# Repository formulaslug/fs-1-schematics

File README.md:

# Summary
This repository contains Kicad schematics and PCB layouts for all electrical systems on FS-1.

# Getting Started
* Install the **Github Flavored Markdown** Chrome extension here: https://chrome.google.com/webstore/detail/github-flavored-markdown/faelggnmhofdamhdegcdhhemfokkfngk?hl=en
* Follow the [Getting Started with Electrical](https://drive.google.com/open?id=1L1viwzrDSNJtUvsPxIs5Tox_gefWKw_3um9R9QZQ264) document in the FS Wiki on the Team Drive.

# Schematics
* [AccumulatorBoardHV](AccumulatorBoardHV/README.md): Board containing Vicor and temperature system DCDC converters, 60V threshold circuit for accumulator indicators, and charging relays
* [AccumulatorBoardLV](AccumulatorBoardLV/README.md): Board containing BMS/temp/IMD fault latching and temperature system.
* [AccumulatorElectronics](AccumulatorElectronics/README.md): Wiring schematic of the Accumulator electronics area
* [BatteryTempMonitor](BatteryTempMonitor/README.md): Single-board temperature system implementation, now split between other Accumulator boards
* [Brake Light](Brake Light/README.md): Brake Light PCB
* [Dash](Dash/README.md): Wiring schematic for dash
* [DashSwitchbox](DashSwitchbox/README.md): Switchbox PCB for Dash
* [PEBoardHV](PEBoardHV/README.md): Board containing discharge circuitry and CAN isolation for Sevcons, as well as 60V threshold circuitry for TSAL
* [PEBoardLV](PEBoardLV/README.md): Board containing ECU, BSPD, and h-bridge to drive TSAL, RTDS, and brake light
* [PEBox](PEBox/README.md): Wiring schematic for power electronics
* [Temperature Shield](Temperature Shield/README.md): Battery Cell Shield, facilitates connections between batteries and the temperature/BMS system
* [TSAL](TSAL/README.md): Board containing TSAL oscillator and LEDs, as well as RTDS piezo

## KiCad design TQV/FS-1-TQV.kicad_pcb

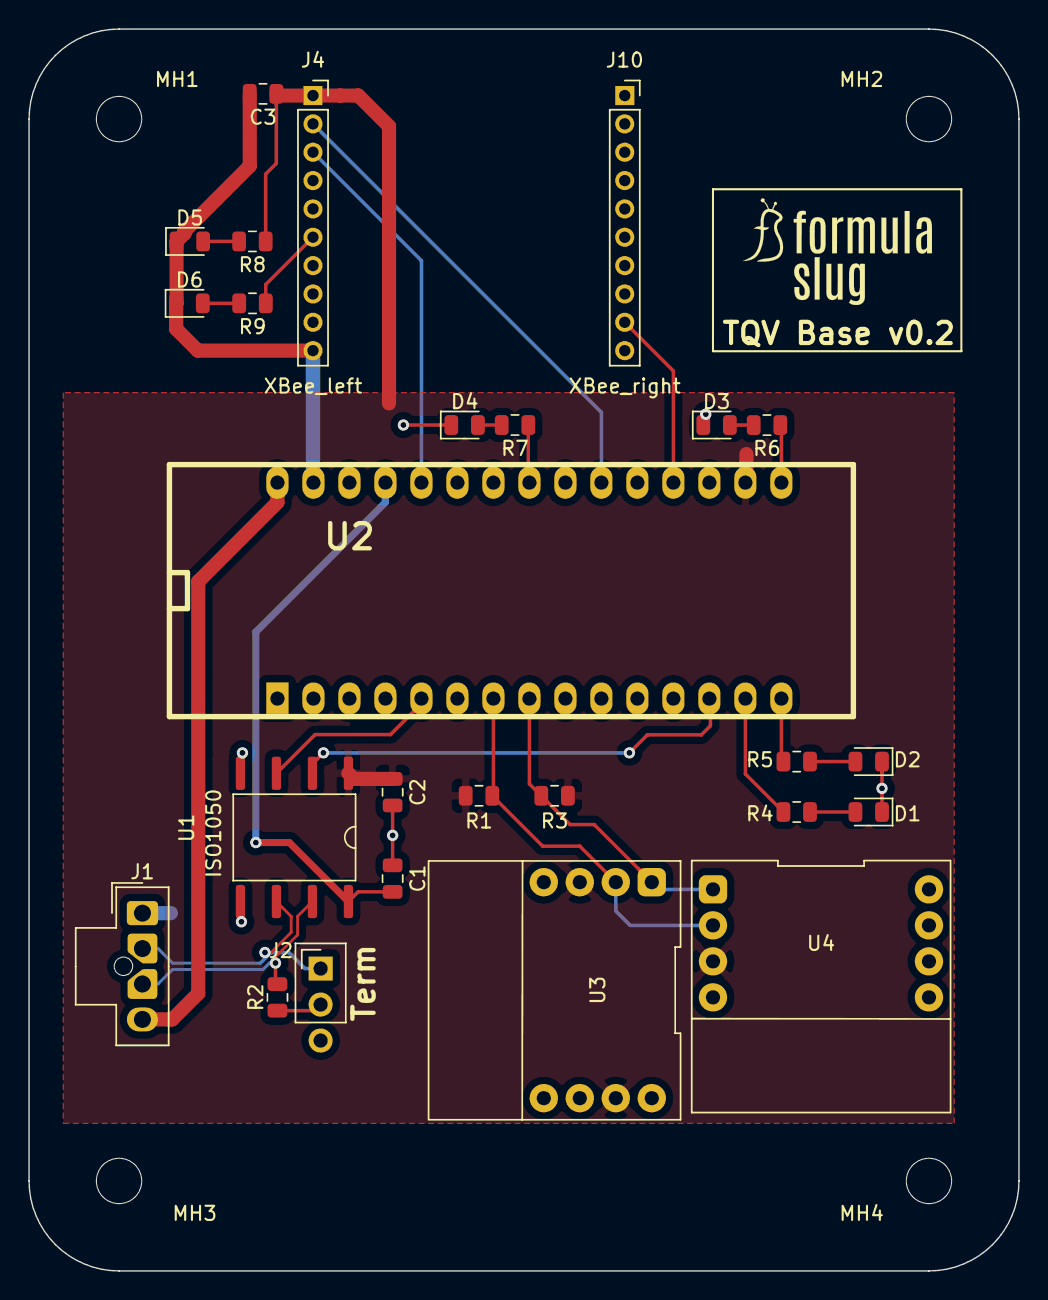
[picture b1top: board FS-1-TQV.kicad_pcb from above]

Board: 2 copper layers, 69.8 x 87.6 mm, 30 parts (0 on the bottom side), 25 nets.

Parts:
C1, C2: 1uF; C_0805_2012Metric
C3: 10uF; C_0805_2012Metric
D1, D2, D3, D4, D5, D6: LED; LED_0805_2012Metric
J1: CAN; Molex_Nano-Fit_1x04_P2.50mm_Vertical_Custom_Pads
J2: Conn_01x03_Male; PinHeader_1x03_P2.54mm_Vertical
J4: XBee_left; PinSocket_1x10_P2.00mm_Vertical
J10: XBee_right; PinSocket_1x10_P2.00mm_Vertical
MH1: MH1; MountingHole_3.2mm_M3
MH2: MH2; MountingHole_3.2mm_M3
MH3: MH3; MountingHole_3.2mm_M3
MH4: MH4; MountingHole_3.2mm_M3
R1, R3: 2k; R_0805_2012Metric
R2, R4, R5, R6, R7: 120; R_0805_2012Metric
R8, R9: 1k; R_0805_2012Metric
U1: ISO1050; SOP-8_6.62x9.15mm_P2.54mm
U2: stm_nucleo_F303K8_fstqv; arduino_mini
U3, U4: SparkFun_MPU9250; Sparkfun_MPU-9250

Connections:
+3V3: C2.2, C3.1, J4.1, R1.2, R3.2, R8.1, U1.1, U2.17, U3.3, U3.7, U4.3
/CAN_N: J1.2, J2.1, U1.6
/CAN_P: J1.3, R2.1, U1.7
GND: C1.2, C2.1, C3.2, D1.1, D2.1, D3.1, D4.1, D5.1, D6.1, J1.1, J4.10, U1.4, U1.5, U2.29, U3.4, U4.4, U4.7
unnamed: C1.1, U1.8, U2.27
unnamed: D1.2, R4.2
unnamed: D2.2, R5.2
unnamed: D3.2, R6.2
unnamed: D4.2, R7.2
unnamed: D5.2, R8.2
unnamed: D6.2, R9.2
unnamed: J1.4, U2.30
unnamed: J2.2, R2.2
unnamed: J4.2, U2.21
unnamed: J4.3, U2.26
unnamed: J4.6, R9.1
unnamed: J10.9, U2.19
unnamed: R1.1, U2.7, U3.2, U4.2
unnamed: R3.1, U2.8, U3.1, U4.1
unnamed: R4.1, U2.14
unnamed: R5.1, U2.15
unnamed: R6.1, U2.16
unnamed: R7.1, U2.23
unnamed: U1.2, U2.13
unnamed: U1.3, U2.5

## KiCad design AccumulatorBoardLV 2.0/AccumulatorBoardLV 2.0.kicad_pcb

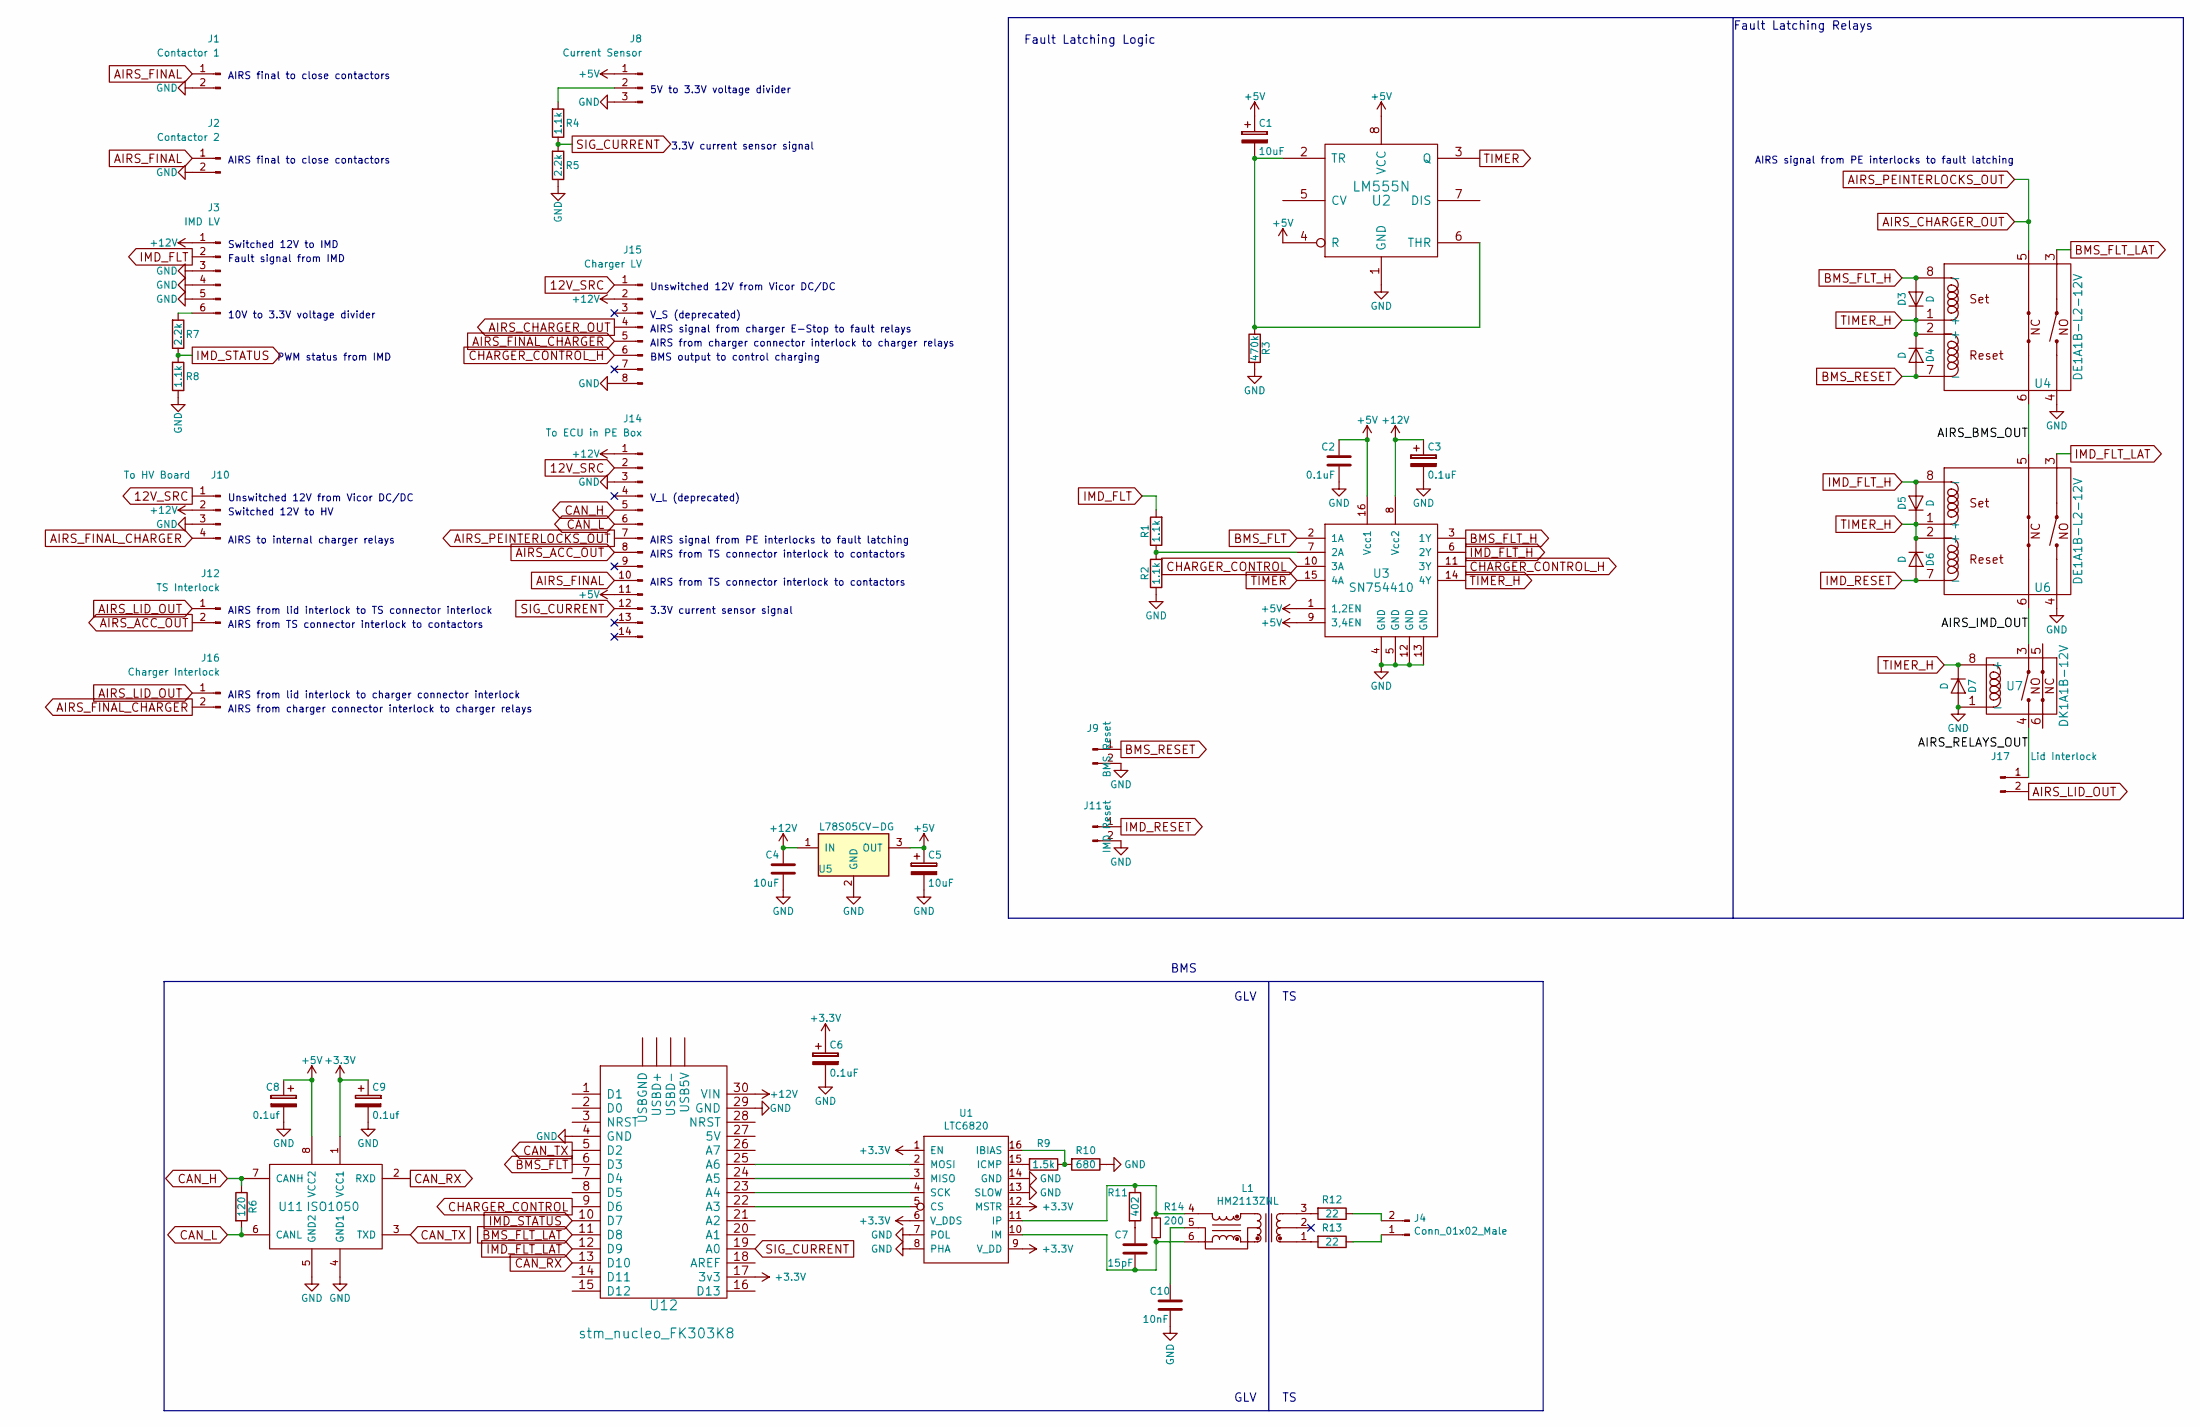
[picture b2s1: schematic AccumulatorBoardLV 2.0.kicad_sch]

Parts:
C1, C4, C5: 10uF; C_0805_HandSoldering
C2, C3, C6: 0.1uF; C_0805_HandSoldering
C7: 15pF; C_0805_HandSoldering
C8, C9: 0.1uf; C_0805_HandSoldering
C10: 10nF; C_0805_HandSoldering
D3, D4, D5, D6, D7: D; D_1206
J1: Contactor 1; Molex_NanoFit_1x02x2.50mm_Straight
J2: Contactor 2; Molex_NanoFit_1x02x2.50mm_Straight
J3: IMD LV; Molex_NanoFit_2x03x2.50mm_Straight
J4: Conn_01x02_Male; Molex_NanoFit_1x02x2.50mm_Straight
J8: Current Sensor; Molex_NanoFit_1x03x2.50mm_Straight
J9: BMS Reset; Molex_NanoFit_1x02x2.50mm_Straight
J10: To HV Board; Molex_NanoFit_2x02x2.50mm_Straight
J11: IMD Reset; Molex_NanoFit_1x02x2.50mm_Straight
J12: TS Interlock; Molex_NanoFit_1x02x2.50mm_Straight
J14: To ECU in PE Box; Ampseal-776261
J15: Charger LV; Ampseal-776276-1
J16: Charger Interlock; Molex_NanoFit_1x02x2.50mm_Straight
J17: Lid Interlock; Molex_NanoFit_1x02x2.50mm_Straight
L1: HM2113ZNL
R1, R2, R4, R8: 1.1k; R_0805_HandSoldering
R3: 470k; R_0805_HandSoldering
R5, R7: 2.2k; R_0805_HandSoldering
R6: 120; R_0805_HandSoldering
R9: 1.5k; R_0805_HandSoldering
R10: 680; R_0805_HandSoldering
R11: 402; R_0805_HandSoldering
R12, R13: 22; R_0805_HandSoldering
R14: 200; R_0805_2012Metric_Pad1.15x1.40mm_HandSolder
U1: LTC6820; MSOP-16_[LTC6820]_10_thou_compat
U2: LM555N; DIP-8_W7.62mm
U3: SN754410; DIP-16_W7.62mm
U4, U6: DE1A1B-L2-12V
U5: L78S05CV-DG; TO-220
U7: DK1A1B-12V
U11: ISO1050; DIP-8_W8.89mm_SMDSocket_LongPads
U12: stm_nucleo_FK303K8; arduino_mini

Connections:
12V_SRC: J10.1, J14.2, J15.1
+3V3: C6.1, C9.1, U1.1 (EN), U1.6 (V_DDS), U1.9 (V_DD), U1.12 (MSTR), U11.1 (VCC1), U12.17 (3v3)
+5V: C1.1, C2.1, C5.1, C8.1, J8.1, J14.11, U2.4 (R), U2.8 (VCC), U3.1 (1,2EN), U3.9 (3,4EN), U3.16 (Vcc1), U5.3 (OUT), U11.8 (VCC2)
+12V: C3.1, C4.1, J3.1, J10.2, J14.1, J15.2, U3.8 (Vcc2), U5.1 (IN), U12.30 (VIN)
/AIRS_BMS_OUT: U4.6, U6.5
/AIRS_IMD_OUT: U6.6, U7.3
/AIRS_RELAYS_OUT: J17.1, U7.4
AIRS_ACC_OUT: J12.2, J14.8
AIRS_CHARGER_OUT: J14.7, J15.4, U4.5
AIRS_FINAL: J1.1, J2.1, J14.10
AIRS_FINAL_CHARGER: J10.4, J15.5, J16.2
AIRS_LID_OUT: J12.1, J16.1, J17.2
BMS_FLT: U3.2 (1A), U12.6 (D3)
BMS_FLT_H: D3.2 (A), U3.3 (1Y), U4.8 (-)
BMS_FLT_LAT: U4.3, U12.11 (D8)
BMS_RESET: D4.2 (A), J9.1, U4.7 (-)
CAN_H: J14.5, R6.1, U11.7 (CANH)
CAN_L: J14.6, R6.2, U11.6 (CANL)
CAN_RX: U11.2 (RXD), U12.13 (D10)
CAN_TX: U11.3 (TXD), U12.5 (D2)
CHARGER_CONTROL: U3.10 (3A), U12.9 (D6)
CHARGER_CONTROL_H: J15.6, U3.11 (3Y)
GND: C2.2, C3.2, C4.2, C5.2, C6.2, C8.2, C9.2, C10.2, D7.2 (A), J1.2, J2.2, J3.3, J3.4, J3.5, J8.3, J9.2, J10.3, J11.2, J14.3, J15.8, R2.1, R3.2, R5.1, R8.1, R10.1, U1.7 (POL), U1.8 (PHA), U1.13 (SLOW), U1.14 (GND), U2.1 (GND), U3.4 (GND), U3.5 (GND), U3.12 (GND), U3.13 (GND), U4.4, U5.2 (GND), U6.4, U7.1 (-), U11.4 (GND1), U11.5 (GND2), U12.4 (GND), U12.29 (GND)
IMD_FLT: J3.2, R1.2
IMD_FLT_H: D5.2 (A), U3.6 (2Y), U6.8 (-)
IMD_FLT_LAT: U6.3, U12.12 (D9)
IMD_RESET: D6.2 (A), J11.1, U6.7 (-)
IMD_STATUS: R7.1, R8.2, U12.10 (D7)
unnamed: C1.2, R3.1, U2.2 (TR), U2.6 (THR)
unnamed: C7.1, R11.2
unnamed: C7.2, L1.6, R14.2, U1.10 (IM)
unnamed: C10.1, L1.5
unnamed: J3.6, R7.2
unnamed: J4.1, R13.1
unnamed: J4.2, R12.1
unnamed: J8.2, R4.2
unnamed: L1.1, R13.2
unnamed: L1.3, R12.2
unnamed: L1.4, R11.1, R14.1, U1.11 (IP)
unnamed: R1.1, R2.2, U3.7 (2A)
unnamed: R9.2, U1.15 (ICMP)
unnamed: R9.1, R10.2, U1.16 (IBIAS)
unnamed: U1.2 (MOSI), U12.25 (A6)
unnamed: U1.3 (MISO), U12.24 (A5)
unnamed: U1.4 (SCK), U12.23 (A4)
unnamed: U1.5 (CS), U12.22 (A3)
SIG_CURRENT: J14.12, R4.1, R5.2, U12.19 (A0)
TIMER: U2.3 (Q), U3.15 (4A)
TIMER_H: D3.1 (K), D4.1 (K), D5.1 (K), D6.1 (K), D7.1 (K), U3.14 (4Y), U4.1 (+), U4.2 (+), U6.1 (+), U6.2 (+), U7.8 (+)

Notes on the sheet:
AIRS signal from PE interlocks to fault latching
AIRS from charger connector interlock to charger relays
AIRS final to close contactors
AIRS from TS connector interlock to contactors
10V to 3.3V voltage divider
AIRS signal from charger E-Stop to fault relays
Unswitched 12V from Vicor DC/DC
3.3V current sensor signal
PWM status from IMD
V_L (deprecated)
V_S (deprecated)
GLV TS
AIRS to internal charger relays
BMS output to control charging
AIRS from lid interlock to TS connector interlock
Switched 12V to HV
BMS
5V to 3.3V voltage divider
AIRS from lid interlock to charger connector interlock
Fault Latching Relays
Fault Latching Logic
Switched 12V to IMD
Fault signal from IMD

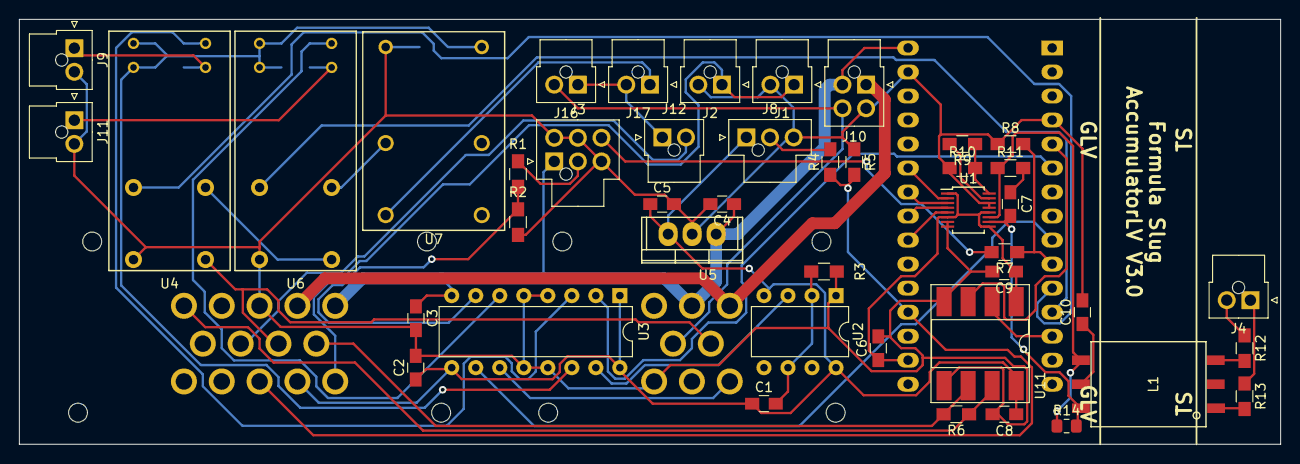
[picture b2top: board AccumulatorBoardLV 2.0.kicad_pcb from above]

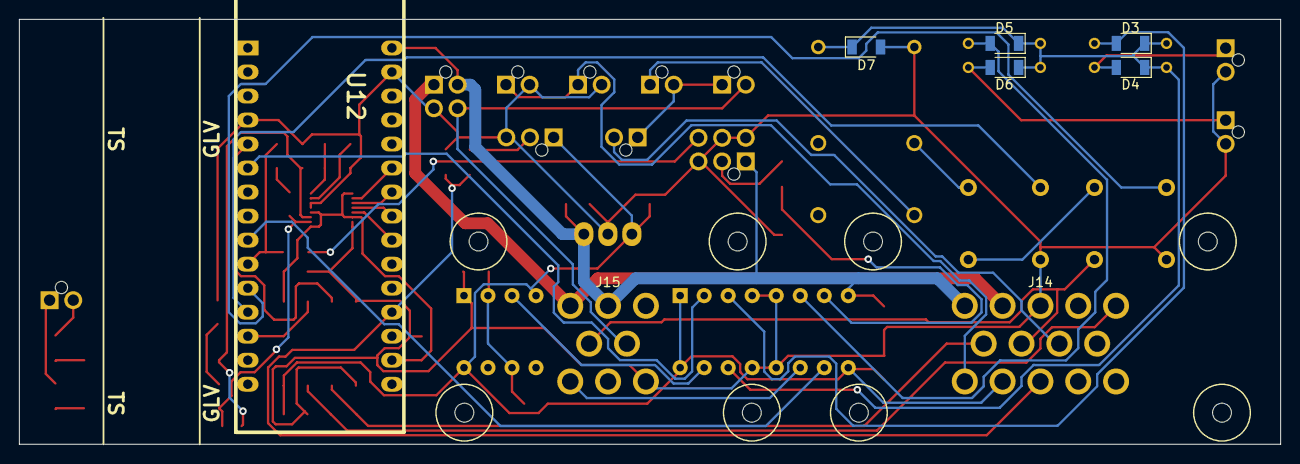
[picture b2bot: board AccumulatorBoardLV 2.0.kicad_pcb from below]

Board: 2 copper layers, 133.4 x 44.9 mm, 52 parts (8 on the bottom side), 49 nets.

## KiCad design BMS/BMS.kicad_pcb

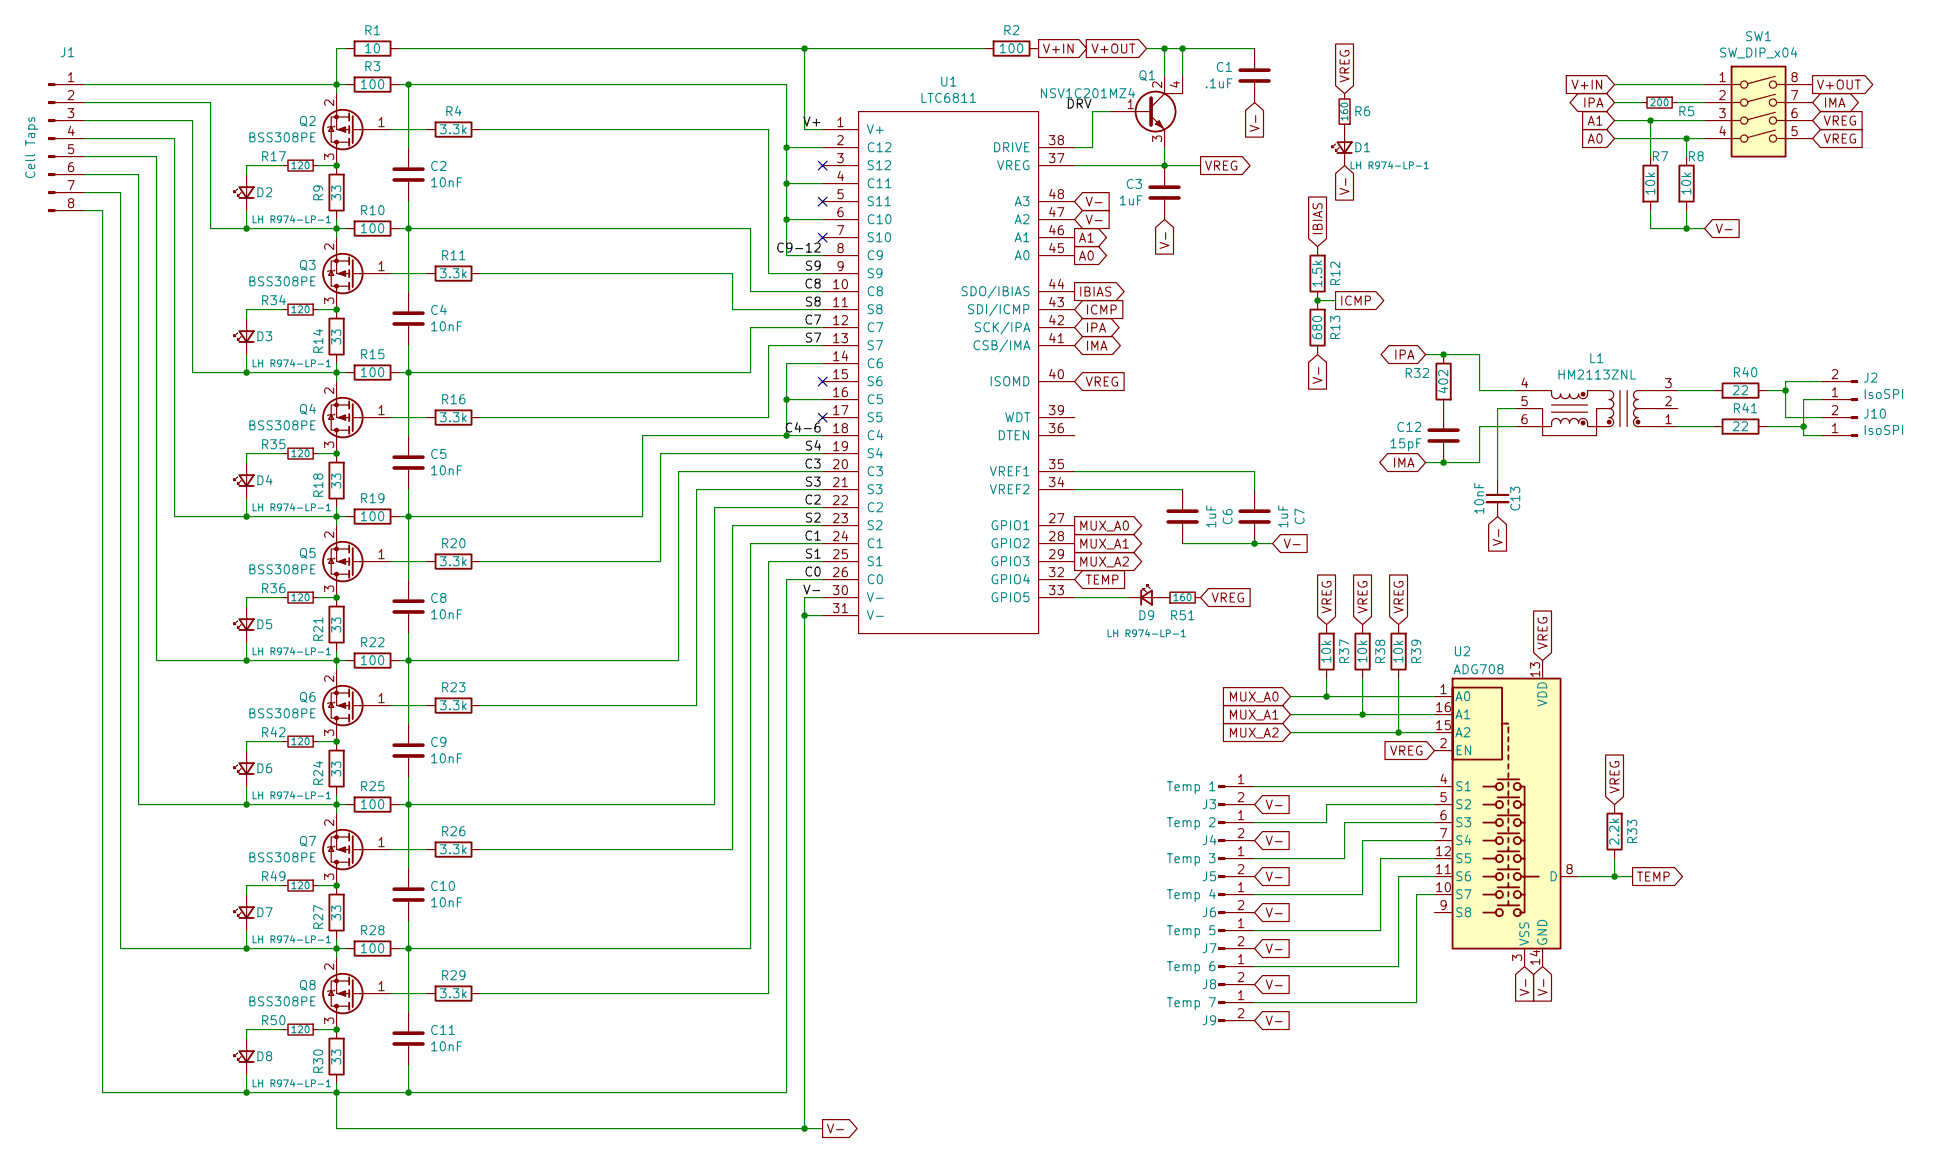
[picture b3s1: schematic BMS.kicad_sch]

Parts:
C1: .1uF; C_0805_HandSoldering
C2, C4, C5, C8, C9, C10, C11, C13: 10nF; C_0805_HandSoldering
C3, C6, C7: 1uF; C_0805_HandSoldering
C12: 15pF; C_0805_HandSoldering
D1, D2, D3, D4, D5, D6, D7, D8, D9: LH R974-LP-1; LED_0805_HandSoldering
J1: Cell Taps
J2, J10: IsoSPI; Molex_NanoFit_1x02x2.50mm_Straight
J3: Temp 1; Molex_NanoFit_1x02x2.50mm_Straight
J4: Temp 2; Molex_NanoFit_1x02x2.50mm_Straight
J5: Temp 3; Molex_NanoFit_1x02x2.50mm_Straight
J6: Temp 4; Molex_NanoFit_1x02x2.50mm_Straight
J7: Temp 5; Molex_NanoFit_1x02x2.50mm_Straight
J8: Temp 6; Molex_NanoFit_1x02x2.50mm_Straight
J9: Temp 7; Molex_NanoFit_1x02x2.50mm_Straight
L1: HM2113ZNL
Q1: NSV1C201MZ4; SOT-223
Q2, Q3, Q4, Q5, Q6, Q7, Q8: BSS308PE; SOT-23
R1: 10; R_0805_HandSoldering
R2, R3, R10, R15, R19, R22, R25, R28: 100; R_0805_HandSoldering
R4, R11, R16, R20, R23, R26, R29: 3.3k; R_0805_HandSoldering
R5: 200; R_0805_HandSoldering
R6, R51: 160; R_0805_HandSoldering
R7, R8, R37, R38, R39: 10k; R_0805_HandSoldering
R9, R14, R18, R21, R24, R27, R30: 33; R_2512_HandSoldering
R12: 1.5k; R_0805_HandSoldering
R13: 680; R_0805_HandSoldering
R17, R34, R35, R36, R42, R49, R50: 120; R_0805_HandSoldering
R32: 402; R_0805_HandSoldering
R33: 2.2k; R_0805_HandSoldering
R40, R41: 22; R_0805_HandSoldering
SW1: SW_DIP_x04; DIP A6H-4101
U1: LTC6811; FSOP-48_[LTC6811-2]
U2: ADG708; TSSOP-16_4.4x5mm_Pitch0.65mm

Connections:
/C1: C10.2, C11.1, R28.1, U1.24 (C1)
/C2: C9.2, C10.1, R25.1, U1.22 (C2)
/C3: C8.2, C9.1, R22.1, U1.20 (C3)
/C4-6: C5.2, C8.1, R19.1, U1.14 (C6), U1.16 (C5), U1.18 (C4)
/C7: C4.2, C5.1, R15.1, U1.12 (C7)
/C8: C2.2, C4.1, R10.1, U1.10 (C8)
/C9-12: C2.1, R3.1, U1.2 (C12), U1.4 (C11), U1.6 (C10), U1.8 (C9)
/DRV: Q1.1 (B), U1.38 (DRIVE)
/S1: R29.1, U1.25 (S1)
/S2: R26.1, U1.23 (S2)
/S3: R23.1, U1.21 (S3)
/S4: R20.1, U1.19 (S4)
/S7: R16.1, U1.13 (S7)
/S8: R11.1, U1.11 (S8)
/S9: R4.1, U1.9 (S9)
/V+: R1.1, R2.2, U1.1 (V+)
A0: R8.1, SW1.4, U1.45 (A0)
A1: R7.1, SW1.3, U1.46 (A1)
IBIAS: R12.2, U1.44 (SDO/IBIAS)
ICMP: R12.1, R13.2, U1.43 (SDI/ICMP)
IMA: C12.1, L1.6, SW1.7, U1.41 (CSB/IMA)
IPA: L1.4, R5.2, R32.1, U1.42 (SCK/IPA)
MUX_A0: R37.1, U1.27 (GPIO1), U2.1 (A0)
MUX_A1: R38.1, U1.28 (GPIO2), U2.16 (A1)
MUX_A2: R39.1, U1.29 (GPIO3), U2.15 (A2)
unnamed: C6.2, U1.34 (VREF2)
unnamed: C7.2, U1.35 (VREF1)
unnamed: C12.2, R32.2
unnamed: C13.1, L1.5
unnamed: D1.2 (A), R6.1
unnamed: D2.1 (K), J1.2, Q3.2 (S), R9.1, R10.2
unnamed: D2.2 (A), R17.2
unnamed: D3.1 (K), J1.3, Q4.2 (S), R14.1, R15.2
unnamed: D3.2 (A), R34.2
unnamed: D4.1 (K), J1.4, Q5.2 (S), R18.1, R19.2
unnamed: D4.2 (A), R35.2
unnamed: D5.1 (K), J1.5, Q6.2 (S), R21.1, R22.2
unnamed: D5.2 (A), R36.2
unnamed: D6.1 (K), J1.6, Q7.2 (S), R24.1, R25.2
unnamed: D6.2 (A), R42.2
unnamed: D7.1 (K), J1.7, Q8.2 (S), R27.1, R28.2
unnamed: D7.2 (A), R49.2
unnamed: D8.2 (A), R50.2
unnamed: D9.1 (K), U1.33 (GPIO5)
unnamed: D9.2 (A), R51.1
unnamed: J1.1, Q2.2 (S), R1.2, R3.2
unnamed: J3.1, U2.4 (S1)
unnamed: J4.1, U2.5 (S2)
unnamed: J5.1, U2.6 (S3)
unnamed: J6.1, U2.7 (S4)
unnamed: J7.1, U2.12 (S5)
unnamed: J8.1, U2.11 (S6)
unnamed: J9.1, U2.10 (S7)
unnamed: J2.1, J10.1, R41.1
unnamed: J2.2, J10.2, R40.1
unnamed: L1.1, R41.2
unnamed: L1.3, R40.2
unnamed: Q2.1 (G), R4.2
unnamed: Q2.3 (D), R9.2, R17.1
unnamed: Q3.1 (G), R11.2
unnamed: Q3.3 (D), R14.2, R34.1
unnamed: Q4.1 (G), R16.2
unnamed: Q4.3 (D), R18.2, R35.1
unnamed: Q5.1 (G), R20.2
unnamed: Q5.3 (D), R21.2, R36.1
unnamed: Q6.1 (G), R23.2
unnamed: Q6.3 (D), R24.2, R42.1
unnamed: Q7.1 (G), R26.2
unnamed: Q7.3 (D), R27.2, R49.1
unnamed: Q8.1 (G), R29.2
unnamed: Q8.3 (D), R30.2, R50.1
unnamed: R5.1, SW1.2
TEMP: R33.1, U1.32 (GPIO4), U2.8 (D)
V+IN: R2.1, SW1.1
V+OUT: C1.1, Q1.2 (C), Q1.4 (C), SW1.8
V-: C1.2, C3.2, C6.1, C7.1, C11.2, C13.2, D1.1 (K), D8.1 (K), J1.8, J3.2, J4.2, J5.2, J6.2, J7.2, J8.2, J9.2, R7.2, R8.2, R13.1, R30.1, U1.26 (C0), U1.30 (V-), U1.31 (V-), U1.47 (A2), U1.48 (A3), U2.3 (VSS), U2.14 (GND)
VREG: C3.1, Q1.3 (E), R6.2, R33.2, R37.2, R38.2, R39.2, R51.2, SW1.5, SW1.6, U1.37 (VREG), U1.40 (ISOMD), U2.2 (EN), U2.13 (VDD)

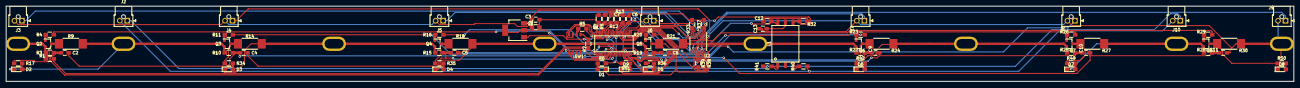
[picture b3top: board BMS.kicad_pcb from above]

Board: 2 copper layers, 428.0 x 25.0 mm, 88 parts (0 on the bottom side), 77 nets.

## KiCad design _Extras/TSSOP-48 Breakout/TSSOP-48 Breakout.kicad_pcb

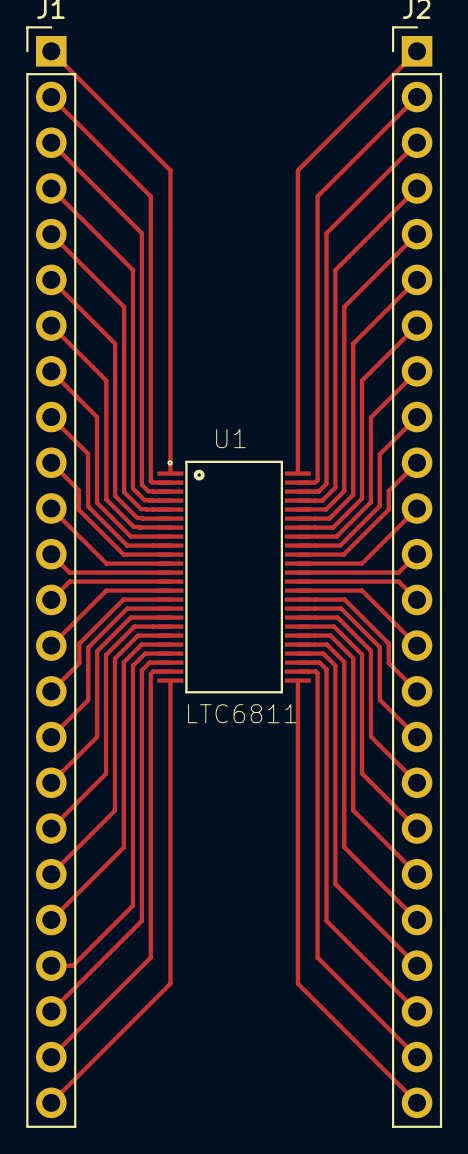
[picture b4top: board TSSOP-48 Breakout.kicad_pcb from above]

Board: 2 copper layers, 3 parts (0 on the bottom side), 48 nets.

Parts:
J1, J2: Conn_01x24_Male; Pin_Header_Straight_1x24_Pitch2.54mm
U1: LTC6811; FSOP-48_[LTC6811-2]_10_thou_compat

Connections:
1: J1.1, U1.1
2: J1.2, U1.2
3: J1.3, U1.3
4: J1.4, U1.4
5: J1.5, U1.5
6: J1.6, U1.6
7: J1.7, U1.7
8: J1.8, U1.8
9: J1.9, U1.9
10: J1.10, U1.10
11: J1.11, U1.11
12: J1.12, U1.12
13: J1.13, U1.13
14: J1.14, U1.14
15: J1.15, U1.15
16: J1.16, U1.16
17: J1.17, U1.17
18: J1.18, U1.18
19: J1.19, U1.19
20: J1.20, U1.20
21: J1.21, U1.21
22: J1.22, U1.22
23: J1.23, U1.23
24: J1.24, U1.24
25: J2.24, U1.25
26: J2.23, U1.26
27: J2.22, U1.27
28: J2.21, U1.28
29: J2.20, U1.29
30: J2.19, U1.30
31: J2.18, U1.31
32: J2.17, U1.32
33: J2.16, U1.33
34: J2.15, U1.34
35: J2.14, U1.35
36: J2.13, U1.36
37: J2.12, U1.37
38: J2.11, U1.38
39: J2.10, U1.39
40: J2.9, U1.40
41: J2.8, U1.41
42: J2.7, U1.42
43: J2.6, U1.43
44: J2.5, U1.44
45: J2.4, U1.45
46: J2.3, U1.46
47: J2.2, U1.47
48: J2.1, U1.48

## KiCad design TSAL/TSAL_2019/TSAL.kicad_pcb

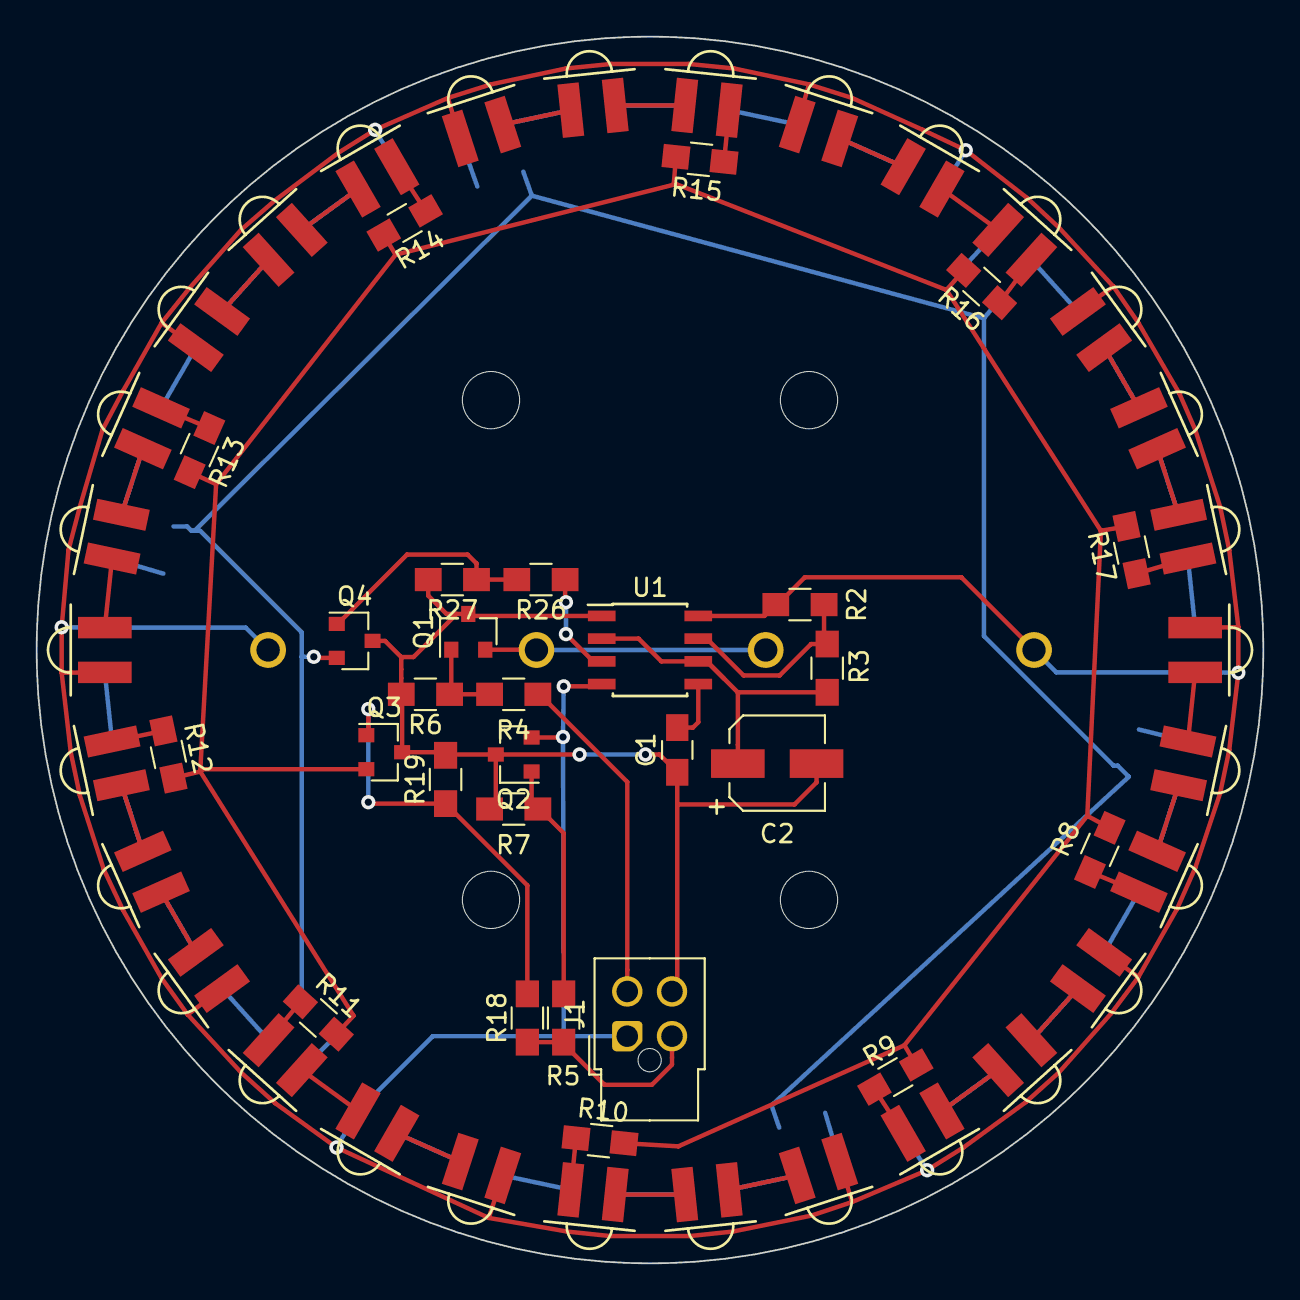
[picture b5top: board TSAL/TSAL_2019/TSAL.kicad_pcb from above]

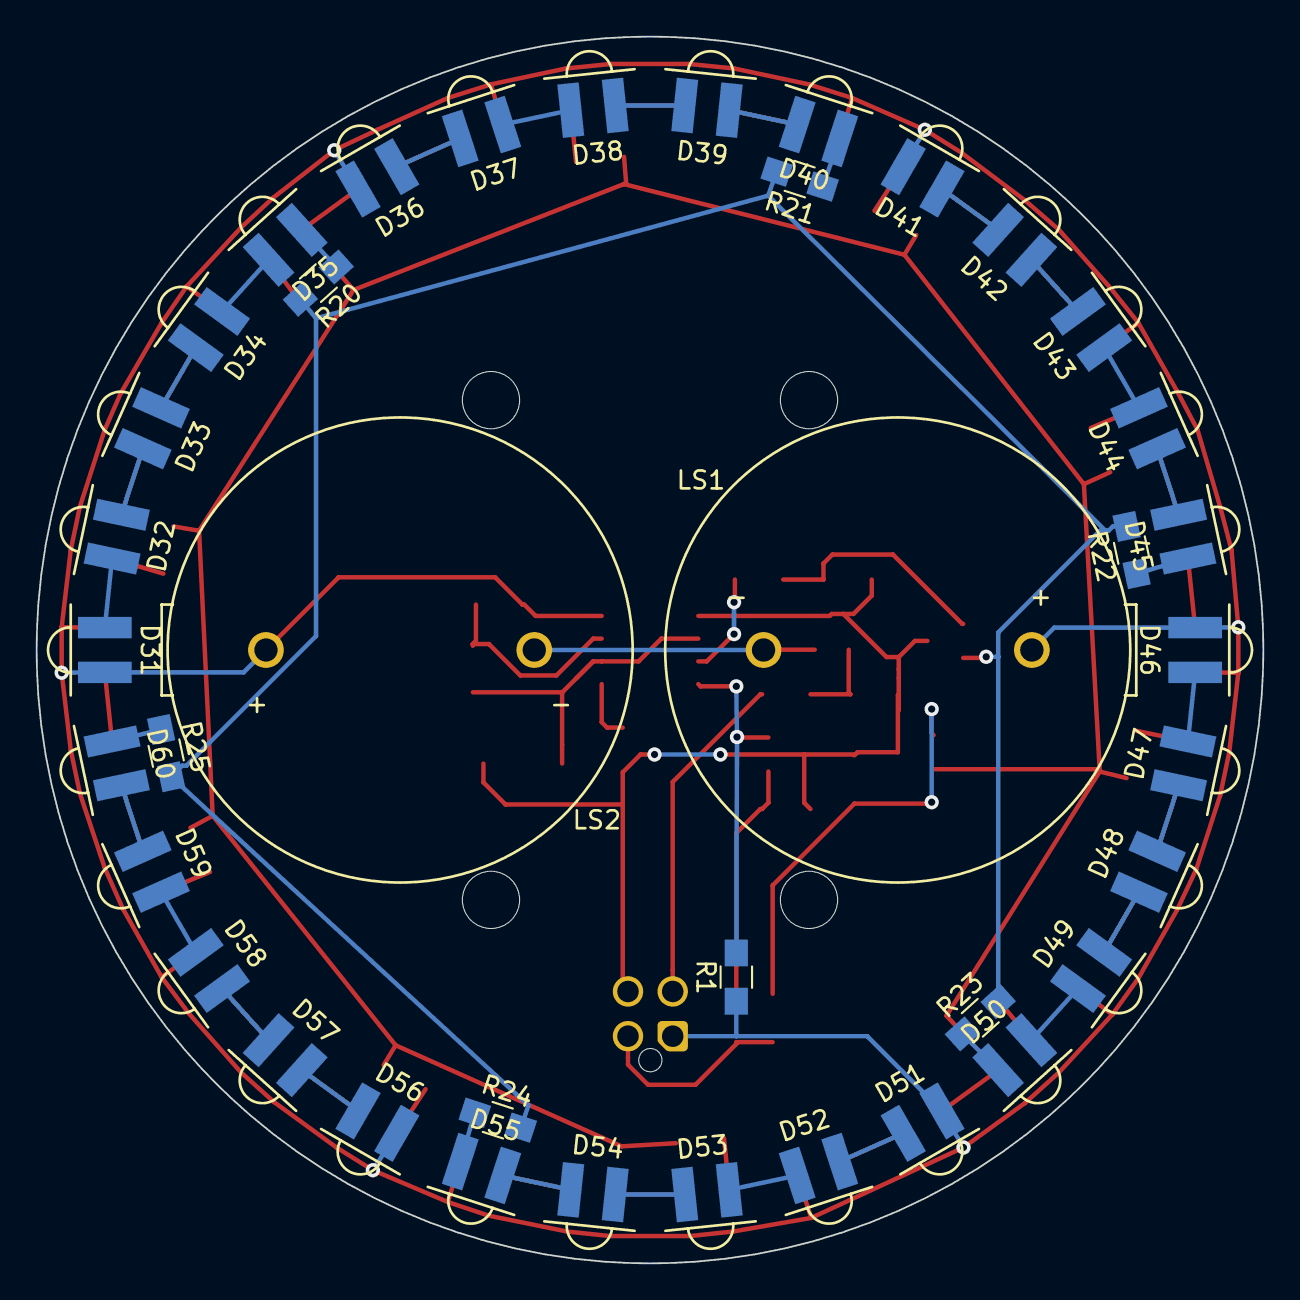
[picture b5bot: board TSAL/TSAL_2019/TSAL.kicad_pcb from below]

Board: 2 copper layers, 68.6 x 68.6 mm, 101 parts (39 on the bottom side), 76 nets.

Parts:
C1: 10uF; C_0805_HandSoldering
C2: 30uF; CP_Elec_5x5.3
D1, D2, D3, D4, D5, D6, D7, D8, D9, D10, D11, D12, D13, D14, D15, D16, D17, D18, D19, D20, D21, D22, D23, D24, D25, D26, D27, D28, D29, D30: LT A6SG-V2AB-35-Z; LED_SMD-2
D31, D32, D33, D34, D35, D36, D37, D38, D39, D40, D41, D42, D43, D44, D45, D46, D47, D48, D49, D50, D51, D52, D53, D54, D55, D56, D57, D58, D59, D60: LR A67F-U2AB-1-1-30-R33-Z; LED_SMD-2
H1, H2, H3, H4: MtngHole; MountingHole_3.2mm_M3
J1: Main Connector; Molex_Nano-Fit_105310-xx04_2x02_P2.50mm_Vertical
LS1, LS2: Speaker; RTDS_H
Q1, Q2, Q3, Q4: TSM320N03CX; SOT-23
R1: 10k; R_0805_HandSoldering
R2, R4, R5, R18, R26: 1k; R_0805_HandSoldering
R3: 5k; R_0805_HandSoldering
R6, R7, R19, R27: 100k; R_0805_HandSoldering
R8, R9, R10, R11, R12, R13, R14, R15, R16, R17: 120; R_0805_HandSoldering
R20, R21, R22, R23, R24, R25: 68; R_0805_HandSoldering
U1: SE555; SOIC-8_3.9x4.9mm_Pitch1.27mm

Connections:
555: R26.1, U1.3
+12V: D1.2, D4.2, D7.2, D10.2, D13.2, D16.2, D19.2, D22.2, D25.2, D28.2, D31.2, D36.2, D41.2, D46.2, D51.2, D56.2, J1.1, LS1.1, LS2.1, R1.1, R2.1, U1.8
GND: C1.1, C2.2, J1.4, Q1.3, Q2.3, Q3.3, Q4.3, R6.2, R7.2, R19.2, R27.2, U1.1
unnamed: C1.2, U1.5
unnamed: C2.1, R3.2, U1.2, U1.6
unnamed: D1.1, D2.2
unnamed: D2.1, D3.2
unnamed: D3.1, R8.1
unnamed: D4.1, D5.2
unnamed: D5.1, D6.2
unnamed: D6.1, R9.1
unnamed: D7.1, D8.2
unnamed: D8.1, D9.2
unnamed: D9.1, R10.1
unnamed: D10.1, D11.2
unnamed: D11.1, D12.2
unnamed: D12.1, R11.1
unnamed: D13.1, D14.2
unnamed: D14.1, D15.2
unnamed: D15.1, R12.1
unnamed: D16.1, D17.2
unnamed: D17.1, D18.2
unnamed: D18.1, R13.1
unnamed: D19.1, D20.2
unnamed: D20.1, D21.2
unnamed: D21.1, R14.1
unnamed: D22.1, D23.2
unnamed: D23.1, D24.2
unnamed: D24.1, R15.1
unnamed: D25.1, D26.2
unnamed: D26.1, D27.2
unnamed: D27.1, R16.1
unnamed: D28.1, D29.2
unnamed: D29.1, D30.2
unnamed: D30.1, R17.1
unnamed: D31.1, D32.2
unnamed: D32.1, D33.2
unnamed: D33.1, D34.2
unnamed: D34.1, D35.2
unnamed: D35.1, R20.1
unnamed: D36.1, D37.2
unnamed: D37.1, D38.2
unnamed: D38.1, D39.2
unnamed: D39.1, D40.2
unnamed: D40.1, R21.1
unnamed: D41.1, D42.2
unnamed: D42.1, D43.2
unnamed: D43.1, D44.2
unnamed: D44.1, D45.2
unnamed: D45.1, R22.1
unnamed: D46.1, D47.2
unnamed: D47.1, D48.2
unnamed: D48.1, D49.2
unnamed: D49.1, D50.2
unnamed: D50.1, R23.1
unnamed: D51.1, D52.2
unnamed: D52.1, D53.2
unnamed: D53.1, D54.2
unnamed: D54.1, D55.2
unnamed: D55.1, R24.1
unnamed: D56.1, D57.2
unnamed: D57.1, D58.2
unnamed: D58.1, D59.2
unnamed: D59.1, D60.2
unnamed: D60.1, R25.1
unnamed: LS1.2, LS2.2, Q1.2
unnamed: Q1.1, R4.2, R6.1
unnamed: Q2.1, R5.2, R7.1
unnamed: Q2.2, R1.2, U1.4
unnamed: Q3.1, R18.2, R19.1
unnamed: Q3.2, R8.2, R9.2, R10.2, R11.2, R12.2, R13.2, R14.2, R15.2, R16.2, R17.2
unnamed: Q4.1, R26.2, R27.1
unnamed: Q4.2, R20.2, R21.2, R22.2, R23.2, R24.2, R25.2
unnamed: R2.2, R3.1, U1.7
SIG_RTDS: J1.3, R4.1
SIG_TSAL: J1.2, R5.1, R18.1

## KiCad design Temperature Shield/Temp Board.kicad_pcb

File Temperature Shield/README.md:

# Summary
[in depth description]

# Notes
* [any important notes to highlight about the system]

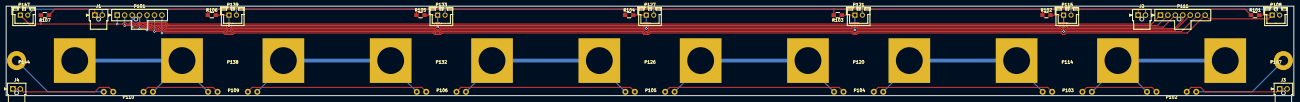
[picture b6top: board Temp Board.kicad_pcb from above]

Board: 2 copper layers, 432.0 x 30.0 mm, 34 parts (0 on the bottom side), 25 nets.

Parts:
J1, J2, J3, J4: Conn_01x02; Molex_NanoFit_1x02x2.50mm_Straight
P101, P111: Conn_01x07; Molex_NanoFit_1x07x2.50mm_Straight
P102: Elithion_7_s; Elithion_R_A
P103: Elithion_6_s; Elithion_R_A
P104: Elithion_5_s; Elithion_R_A
P105: Elithion_4_s; Elithion_R_A
P106: Elithion_3_s; Elithion_R_A
P107: Energus 7; Energus_End_R
P108: 7_temp; JST_XH_B02B-XH-A_02x2.50mm_Straight
P109: Elithion_2_s; Elithion_R_A
P110: Elithion_1_s; Elithion_R_A
P114: Energus 6; Energus
P115: 6_temp; JST_XH_B02B-XH-A_02x2.50mm_Straight
P120: Energus 5; Energus
P121: 5_temp; JST_XH_B02B-XH-A_02x2.50mm_Straight
P126: Energus 4; Energus
P127: 4_temp; JST_XH_B02B-XH-A_02x2.50mm_Straight
P132: Energus 3; Energus
P133: 3_temp; JST_XH_B02B-XH-A_02x2.50mm_Straight
P138: Energus 2; Energus
P139: 2_temp; JST_XH_B02B-XH-A_02x2.50mm_Straight
P144: Energus 1; Energus_End_L
P147: 1_temp; JST_XH_B02B-XH-A_02x2.50mm_Straight
R101, R102, R103, R104, R105, R106, R107: 2.2K; R_0805_HandSoldering

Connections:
1_B+: P109.B-, P110.B+, P138.2, P144.1
1_B-: P110.B-, P144.2
1_C+: P109.C-, P110.C+
1_C-: J4.1, J4.2, P110.C-
1_temp: P101.1, P111.1, P147.1, R107.2
2_B+: P106.B-, P109.B+, P132.2, P138.1
2_C+: P106.C-, P109.C+
2_temp: P101.2, P111.2, P139.1, R106.2
3_B+: P105.B-, P106.B+, P126.2, P132.1
3_C+: P105.C-, P106.C+
3_temp: P101.3, P111.3, P133.1, R105.2
4_B+: P104.B-, P105.B+, P120.2, P126.1
4_C+: P104.C-, P105.C+
4_temp: P101.4, P111.4, P127.1, R104.2
5_B+: P103.B-, P104.B+, P114.2, P120.1
5_C+: P103.C-, P104.C+
5_temp: P101.5, P111.5, P121.1, R103.1
6_B+: P102.B-, P103.B+, P107.2, P114.1
6_C+: P102.C-, P103.C+
6_temp: P101.6, P111.6, P115.1, R102.2
7_B+: P102.B+, P107.1
7_C+: J3.1, J3.2, P102.C+
7_temp: P101.7, P108.1, P111.7, R101.2
+3V3: J1.1, J2.1, R101.1, R102.1, R103.2, R104.1, R105.1, R106.1, R107.1
GND: J1.2, J2.2, P108.2, P115.2, P121.2, P127.2, P133.2, P139.2, P147.2
